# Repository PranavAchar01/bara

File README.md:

<p align="center">
  
</p>

<p align="center">
  <b>Describe a device. Get it built from real parts.</b><br />
  A <b>Cal Hacks 13.0</b> project by Pranav Achar and Nithin Aruswamy · <a href="https://tangible.parts">tangible.parts</a>
</p>

---

<p align="center">
  <b><a href="https://youtu.be/Tw2DHo8dgQ8">▶ Watch the 3-minute demo</a></b>
</p>

Type "a wireless split keyboard with an OLED" and watch it come together. Bara picks real parts, lays them out in 3D, sculpts a case, routes a real KiCad board, and writes the firmware, explaining every choice as it goes. Then you change it in plain words or with your voice, and every edit is checked before it lands.

## Inside the app

<table>
  <tr>
    <td width="50%"><br /><b>Start</b> · describe a device in one line</td>
    <td width="50%"><br /><b>Edit</b> · click a part to swap, recolour, move, or ask</td>
  </tr>
  <tr>
    <td><br /><b>Explode</b> · pull it apart and see every layer</td>
    <td><br /><b>Board</b> · a routed KiCad PCB that passes DRC</td>
  </tr>
  <tr>
    <td><br /><b>Simulate</b> · run the generated firmware and press the keys</td>
    <td><br /><b>Library</b> · past builds and 135 open-source boards</td>
  </tr>
</table>

## Meet Bara

Bara is the agent who builds with you: an ink oval with two eyes, nothing else. It walks onto the canvas, hovers over the part it's choosing, and shows how it feels through motion alone. Click a part to swap it, recolour it, move it, or ask about it. Hold <kbd>Space</kbd> to talk. Every change lands as a version you can undo.

<br clear="right" />

## What it builds

Each of these started as one sentence.

## Tangible vs a general chat model

We gave Claude (Fable 5.1, a fresh chat on claude.ai) the prompt "an ergonomic mouse with a PAW3212 optical sensor, two main click switches, a scroll wheel encoder and an nRF52840 board", and compared what it produced with a Tangible build of the same kind of mouse.

| | Claude (Fable 5.1) | Tangible |
|---|---|---|
| First reply | Text only: a pin map and a bill of materials (33 s) | An existing library build, so no new run was timed |
| 3D model | Only after a follow-up asking for one: a Three.js page you can rotate (150 s) | Built in |
| Exploded view | Only after a second follow-up (59 s) | Built in |
| Part shapes | Procedural boxes and cylinders | KiCad library part models on a routed PCB |
| Board and export | A PCB shape and a shell, with no routed board and no export | A routed KiCad board and a case |

It took Claude two follow-ups to get to an exploded 3D view. That viewer does work well: you can rotate it, X-ray it, flip to the underside and drag an explode slider.

The Tangible build here is an existing, larger version of the mouse from the library (extra thumb switches, a slide switch, an IMU, a proximity sensor and a battery connector), not a fresh run against the same prompt. It also lists one push button, where the prompt asked for two main click switches. Screenshots were taken at different sizes: Claude at 1200x1189 with its chat pane, Tangible at 1600x1000.

<table>
  <tr>
    <td width="50%"><br /><b>Claude, assembled</b></td>
    <td width="50%"><br /><b>Claude, exploded</b></td>
  </tr>
  <tr>
    <td><br /><b>Tangible, assembled</b></td>
    <td><br /><b>Tangible, exploded</b></td>
  </tr>
</table>

In a separate measurement for the demo video, a general coding agent given a handheld-console prompt took 50.4 s and answered with text and a browser game.

## How a build works

```mermaid
flowchart LR
  P([Your prompt]) --> S[Scout open designs]
  S --> C[Classify and compose]
  C --> L[Place parts]
  L --> E[Sculpt the case]
  E --> B[Route the board]
  B --> F[Write firmware]
  F --> R([3D build you can edit])
  R -. voice or text edits .-> C

  classDef you fill:#2563EB,color:#fff,stroke:#2563EB
  classDef claude fill:#D97757,color:#fff,stroke:#D97757
  classDef kicad fill:#161616,color:#fff,stroke:#161616
  class S you
  class C,F claude
  class B kicad
```

<table>
  <tr><td>🔵 <b>Scout</b></td><td>Finds open designs that already exist, so Bara reuses before it invents.</td></tr>
  <tr><td>🟠 <b>Compose</b></td><td>Breaks the device into function blocks and picks one real part for each, with reasons.</td></tr>
  <tr><td>⚫ <b>Board</b></td><td>pcbnew builds it, Freerouting routes it, kicad-cli checks it. DRC errors trigger a re-route.</td></tr>
  <tr><td>✅ <b>Checks</b></td><td>Electrical, mechanical, and a vision judge that asks if it actually looks like the device.</td></tr>
</table>

## Sponsor tools

| | Tool | What it does in Bara |
|---|---|---|
| 🟠 | **Anthropic Claude** | The engineer behind every decision. Sonnet 5.5 classifies the prompt, asks clarifying questions, picks parts (schema-locked to real part IDs), writes firmware, judges the render, and handles edits. Claude Code built the product, including an overnight loop that ran our test prompts, found root causes, and pushed fixes. |
| 🟣 | **Figma** | All design, made through Claude Code and the Figma MCP. FigJam teardown, a full design system with the agent's moods, a Make prototype of explode and focus, and design tokens pulled straight into `tokens.css`. |
| 🟢 | **OpenAI** | Bara's voice. gpt-4o-mini-tts speaks with a written personality, and gpt-4o-transcribe listens, hinted with the build's part names so "SSD1306" comes through right. |
| 🔵 | **You.com** | The first search on every build. Finds open designs with a real KiCad board, plus photos of the real product so the case looks right. |
| 🟩 | **Apify** | The Open Hardware Scout Actor ([actors/](actors/bara-hardware-scout)). Fallback search, and it prices every part so the BOM has live stock and buy links. |
| 🔶 | **Cerebras** | A fast path for quick, constrained calls, with Claude as backup and keyword rules as the last resort, so a build always finishes. |

## Fit check (OpenCV 5 on AWS)

Built for the OpenCV AI Competition 2026, after Cal Hacks. Lay a printed ArUco marker next to the space a device has to fit and take one photo from above. OpenCV 5 on AWS Lambda (arm64 Graviton) rectifies the photo and measures the space in millimetres. The agent then proposes the next step: build to that size, shrink the current case, cut its height, or retake the photo if it can't trust it. Nothing changes until you approve.

On synthetic photos with known sizes the mean error is 0.42 mm (p95 1.4 mm), and bad photos get a retake request in 29 of 30 cases. The [technical report](docs/hackathons/opencv26/report.md) covers the method, the deployment, the evaluation and its limits.

```bash
cd server && uv run pytest tests/test_vision.py
uv run python scripts/vision_eval.py ../docs/hackathons/opencv26/eval
uv run python aws/deploy.py        # needs AWS credentials in the environment
```

## Run it

You need [uv](https://docs.astral.sh/uv/), [pnpm](https://pnpm.io), and Node.

```bash
scripts/dev.sh
```

That starts the engine on `127.0.0.1:8790` and the app on http://localhost:5173. No keys? Open http://localhost:5173/?mock=1 to replay a recorded build in the browser.

Live builds need `ANTHROPIC_API_KEY`, plus KiCad 10 and Freerouting for boards. `OPENAI_API_KEY`, `YOU_API_KEY`, `APIFY_TOKEN`, and `CEREBRAS_API_KEY` are optional. Keys come from the environment only.

<details>
<summary>Tests and repo layout</summary>

```bash
cd server && uv run pytest
cd web && pnpm test
scripts/e2e.sh
```

```
spec/      the contract between app and engine (SPEC.md, schemas, fixtures)
server/    FastAPI engine (src/bara), catalog and assets in data/
web/       Vite + React + React Three Fiber app
actors/    the Apify Open Hardware Scout
scripts/   dev, e2e, deploy, and render scripts
```

</details>

## Disclosure

Before the event we wrote the spec and a labelled set of test prompts, and ran a small routing experiment to check the idea was feasible. None of that experiment's code is in this repo. We used Nithin's public UI skill library, the same one we used in Etch. Everything in this repo was written at Cal Hacks 13.0.

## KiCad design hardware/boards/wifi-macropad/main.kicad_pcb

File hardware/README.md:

# Hardware gate

Tangible turns a sentence into a gadget: parts, a KiCad schematic and PCB, and a printed shell.
This folder holds boards Tangible generated, and the gate every board passes before it ships.

- `boards/<board>/` holds `main.kicad_pcb`, `main.kicad_sch`, `main.kicad_pro` and `fp-lib-table`.
  Library paths use `${TANGIBLE_ROOT}`, `${TANGIBLE_SOURCES}` and `${KICAD10_FOOTPRINT_DIR}`.
- `policy.json` sets the gate (0 DRC errors, 0 ERC errors, 0 unconnected items, 0 blocked parts)
  and maps each footprint library to its source and licence.

Run it locally (needs `kicad-cli` 10):

```sh
PYTHONPATH=server/src python3 -m bara.hwci check hardware/boards --policy hardware/policy.json
PYTHONPATH=server/src python3 -m bara.hwci fab hardware/boards --out hw-fab
```

`check` writes `hw-report/`: `results.json`, `gate.md` (the merge request note), `junit.xml`,
`gl-code-quality-report.json` and a CycloneDX hardware BOM per board in `hbom/`.

The same checks are an MCP server for GitLab Duo (`.gitlab/duo/mcp.json`):

```sh
PYTHONPATH=server/src python3 -m bara.hwci.mcp_server --root hardware/boards --policy hardware/policy.json
```

Tools: `list_boards`, `check_board`, `board_parts`, `export_fab`.

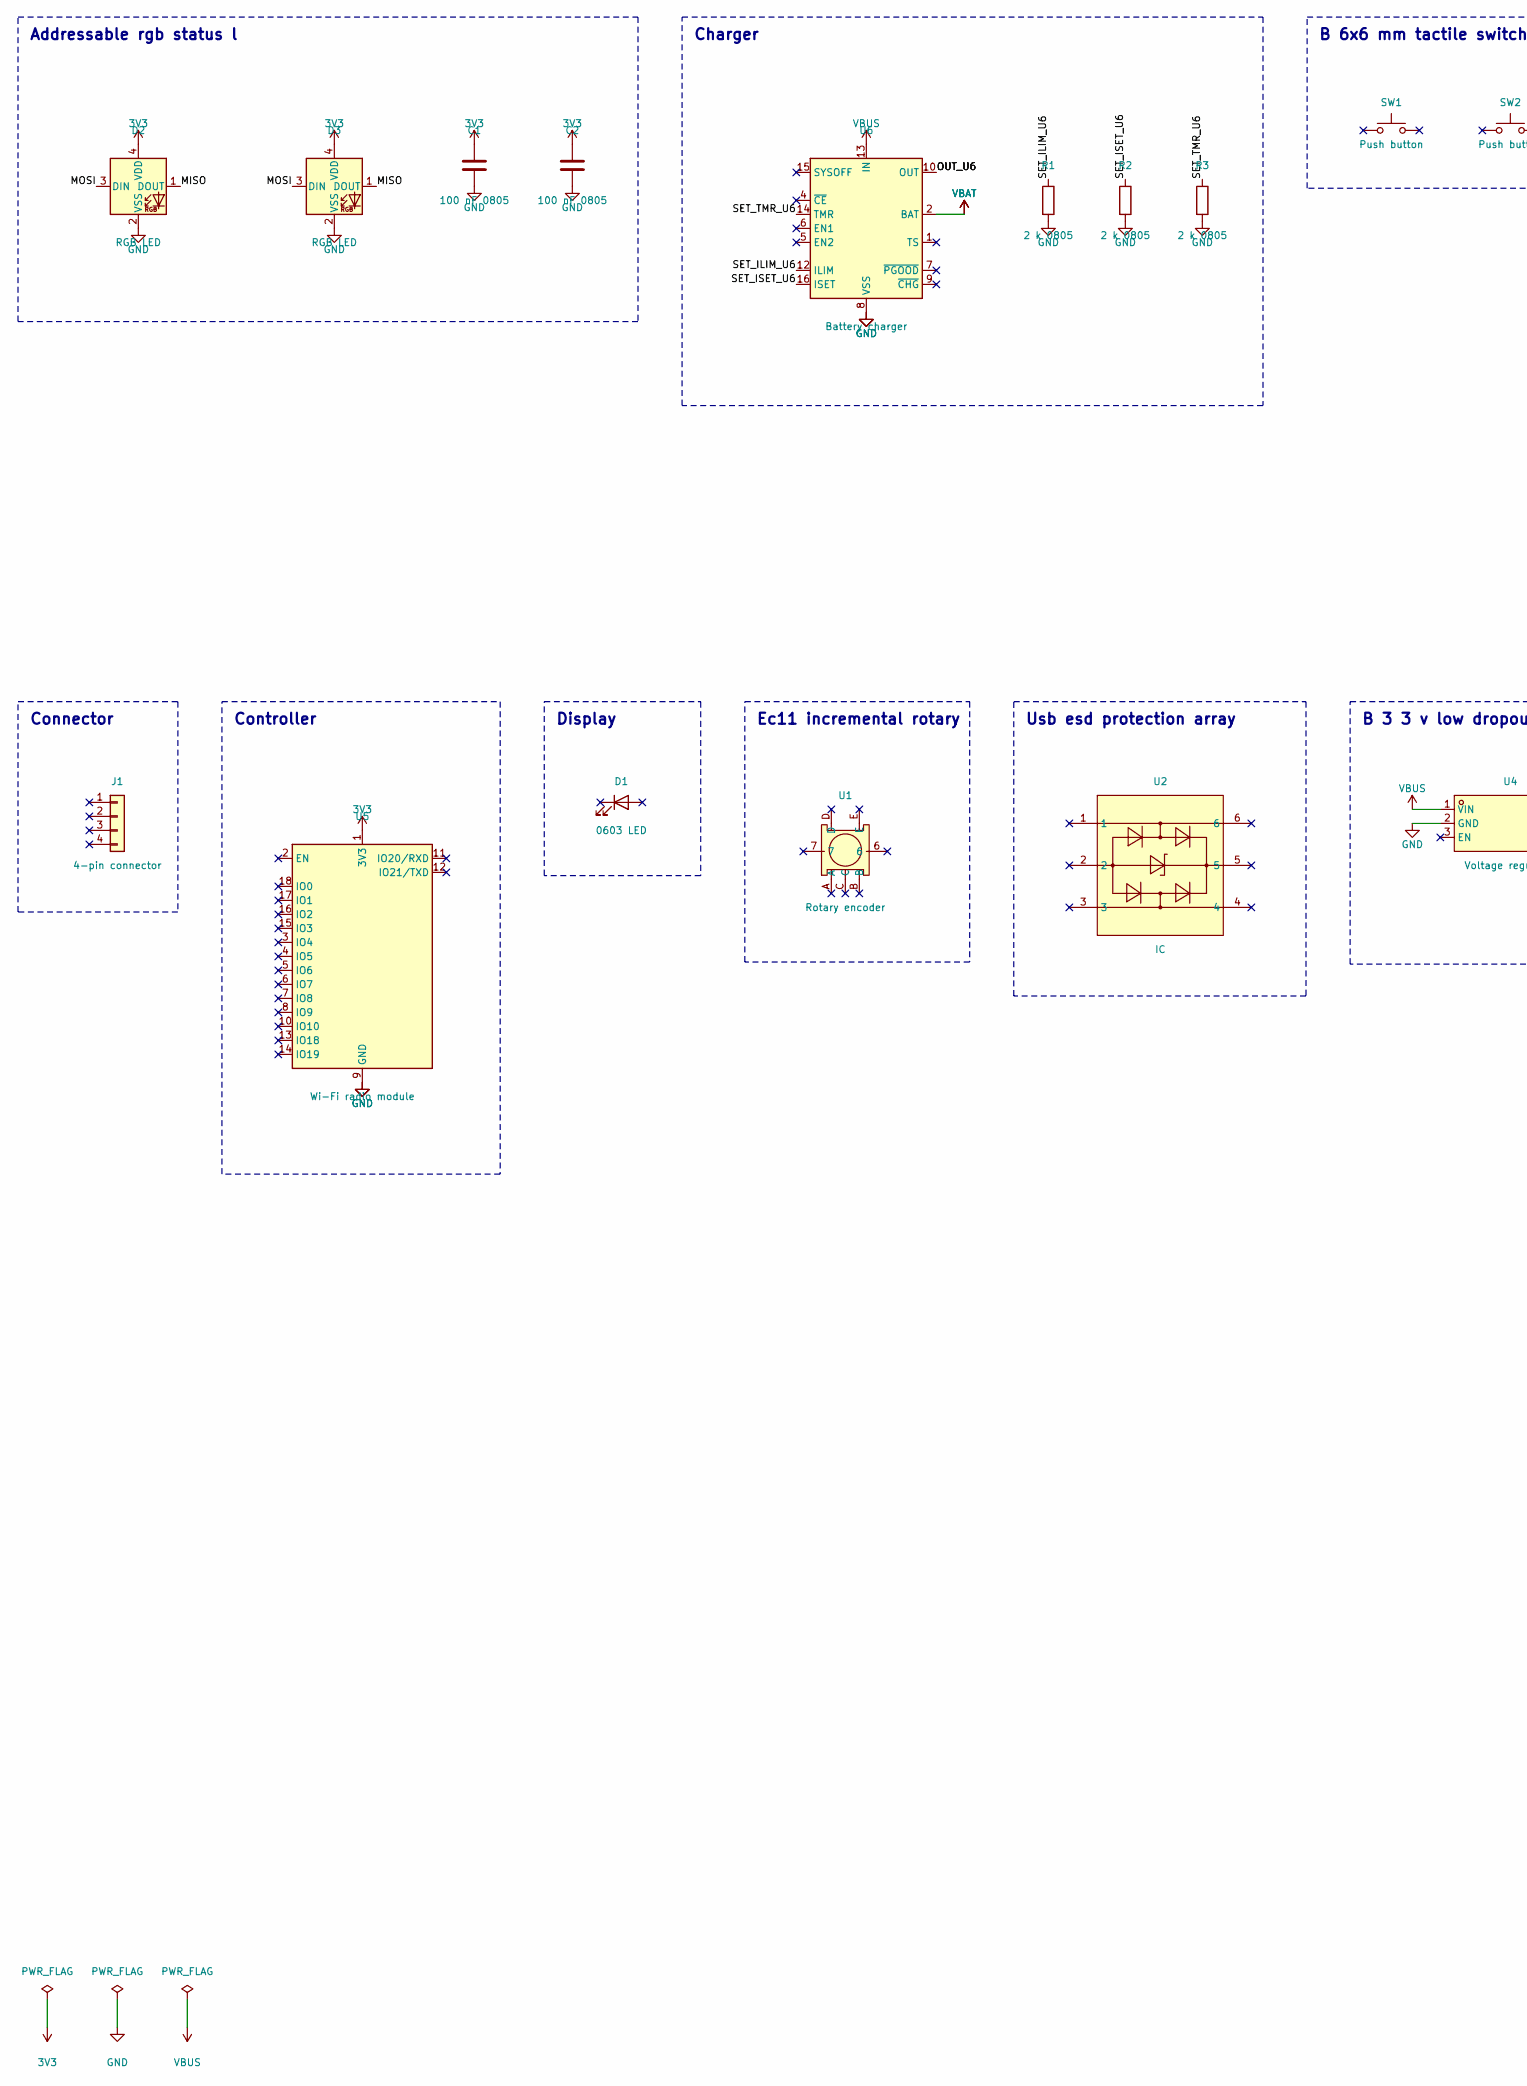
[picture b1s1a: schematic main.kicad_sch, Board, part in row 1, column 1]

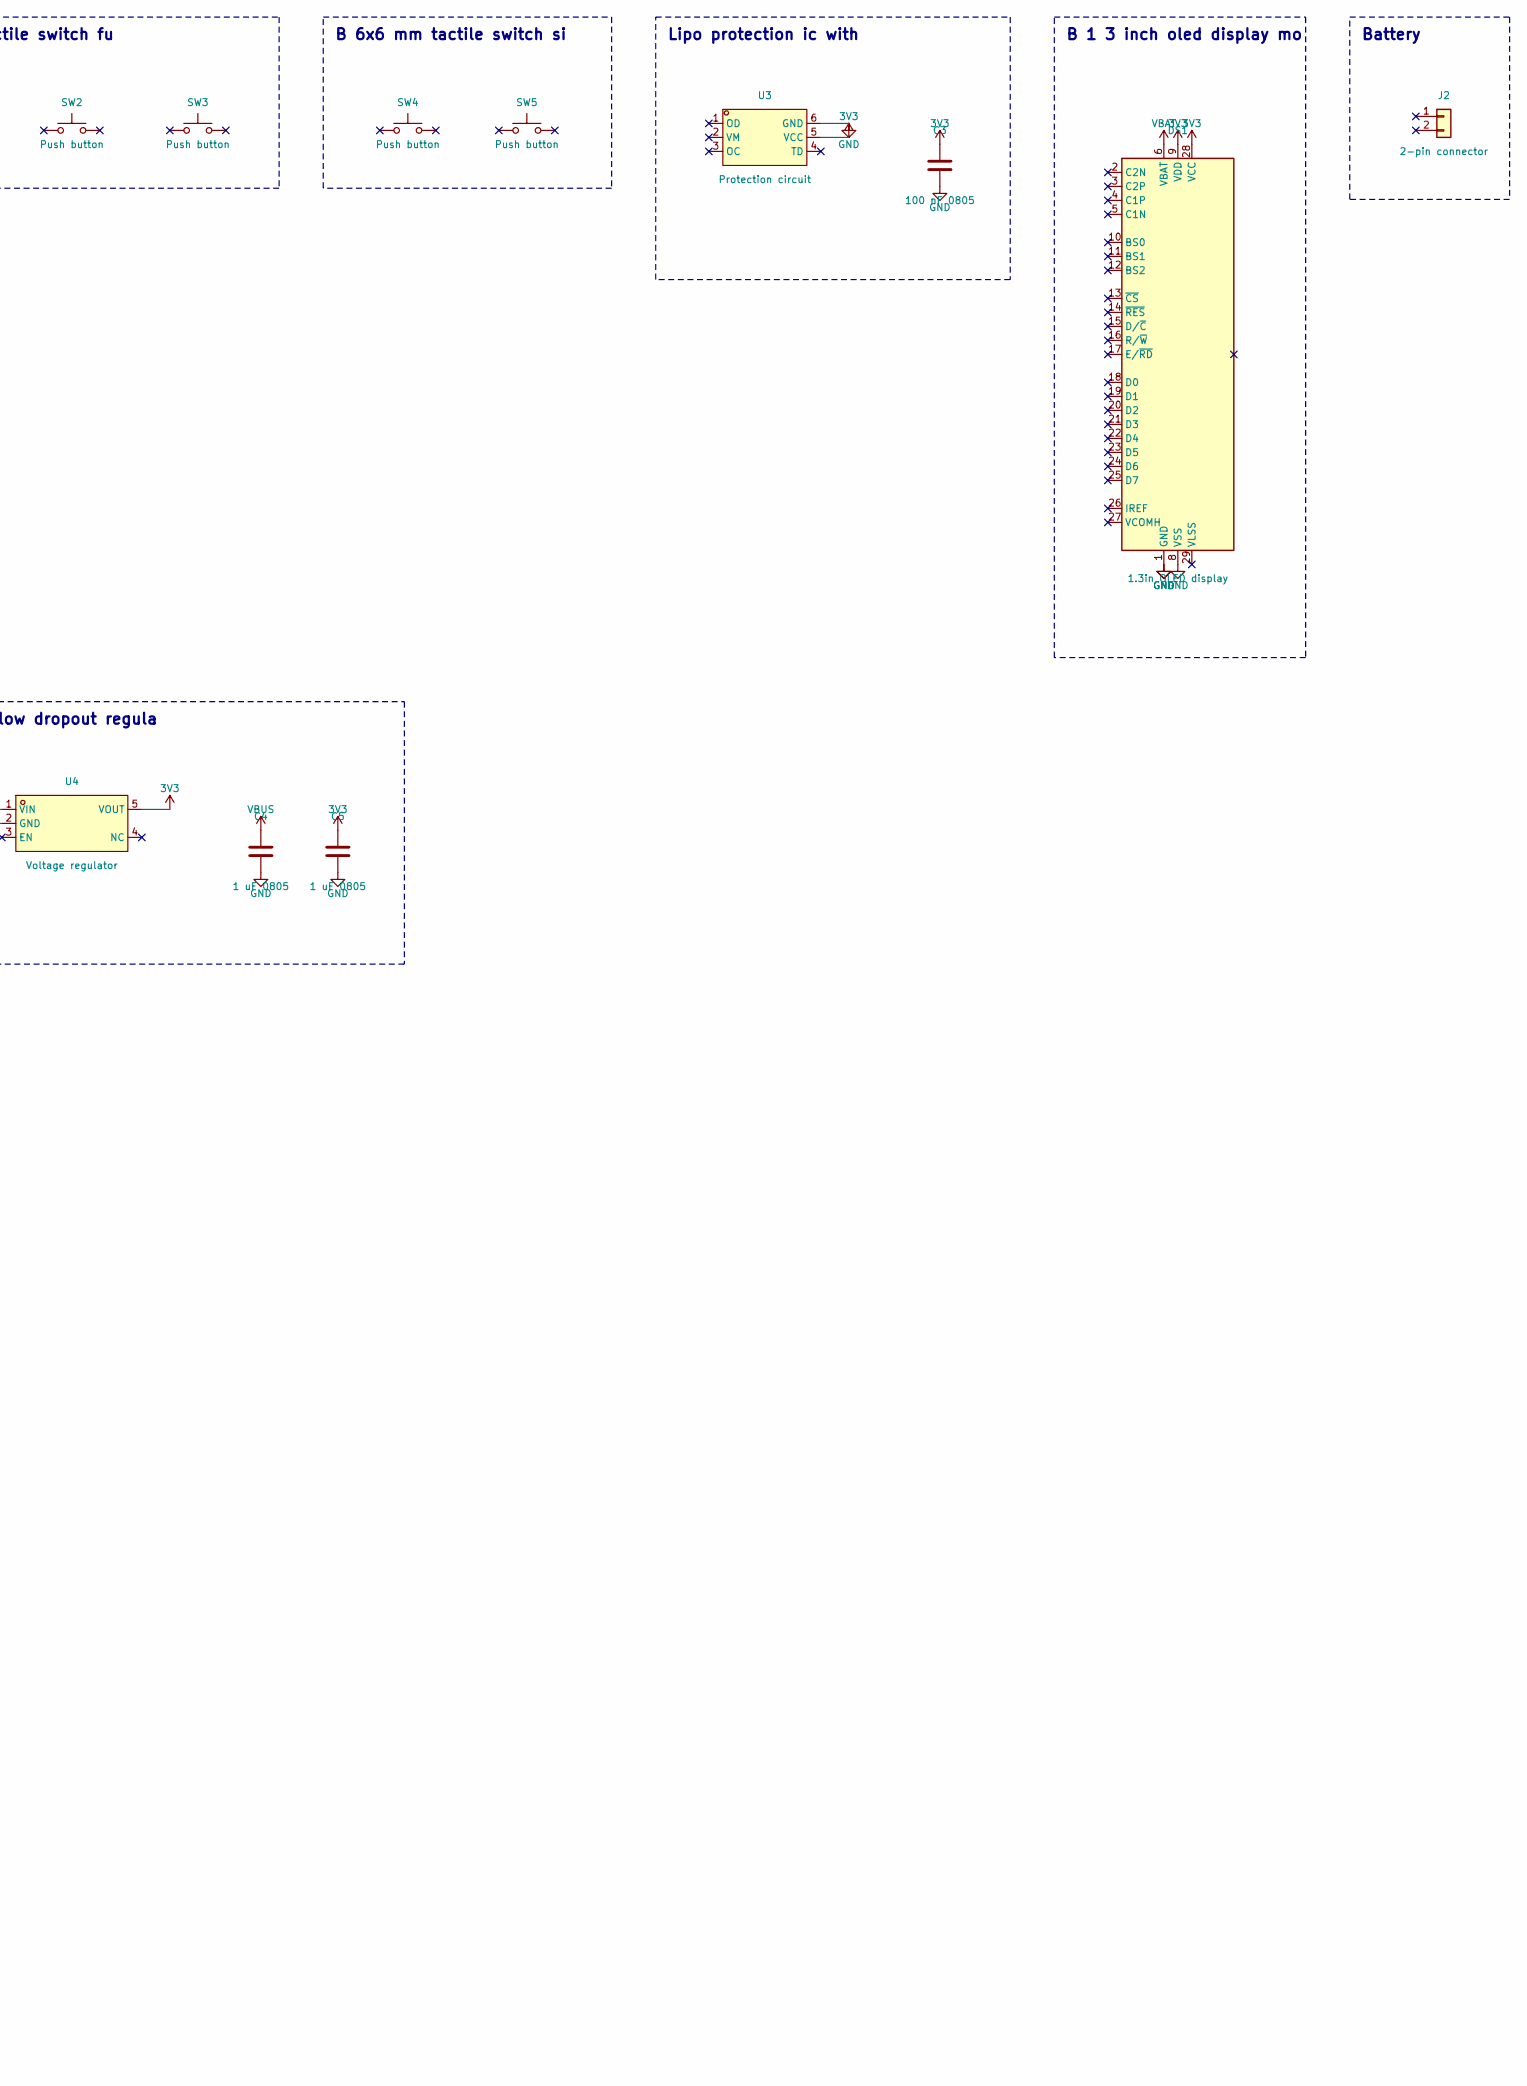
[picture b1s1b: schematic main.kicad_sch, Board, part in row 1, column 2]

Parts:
C1, C2, C3: 100 nF 0805; C_0805_2012Metric
C4, C5: 1 uF 0805; C_0805_2012Metric
D1: 0603 LED; LED_0603_1608Metric
D2, D3: RGB LED; LED_WS2812B-2020_PLCC4_2.0x2.0mm
DS1: 1.3in OLED display; OLED-128O064D
J1: 4-pin connector; JST_SH_SM04B-SRSS-TB_1x04-1MP_P1.00mm_Horizontal
J2: 2-pin connector; JST_PH_S2B-PH-K_1x02_P2.00mm_Horizontal
R1, R2, R3: 2 k 0805; R_0805_2012Metric
SW1, SW2, SW3, SW4, SW5: Push button; SW_PUSH_6mm
U1: Rotary encoder; C370970
U2: IC; C7519
U3: Protection circuit; C351410
U4: Voltage regulator; C51118
U5: Wi-Fi radio module; ESP32-C3-WROOM-02
U6: Battery charger; VQFN-16-1EP_3x3mm_P0.5mm_EP1.68x1.68mm

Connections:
3V3: C1.1, C2.1, C3.1, C5.1, D2.4 (VDD), D3.4 (VDD), DS1.9 (VDD), DS1.28 (VCC), U3.5 (VCC), U4.5 (VOUT), U5.1 (3V3)
GND: C1.2, C2.2, C3.2, C4.2, C5.2, D2.2 (VSS), D3.2 (VSS), DS1.1 (GND), DS1.8 (VSS), DS1.30 (GND), R1.2, R2.2, R3.2, U3.6 (GND), U4.2 (GND), U5.9 (GND), U5.19 (GND), U6.8 (VSS), U6.17 (VSS)
MISO: D2.1 (DOUT), D3.1 (DOUT)
MOSI: D2.3 (DIN), D3.3 (DIN)
OUT_U6: U6.10 (OUT), U6.11 (OUT)
SET_ILIM_U6: R1.1, U6.12 (ILIM)
SET_ISET_U6: R2.1, U6.16 (ISET)
SET_TMR_U6: R3.1, U6.14 (TMR)
VBAT: DS1.6 (VBAT), U6.2 (BAT), U6.3 (BAT)
VBUS: C4.1, U4.1 (VIN), U6.13 (IN)

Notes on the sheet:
Addressable rgb status l
Charger
B 6x6 mm tactile switch fu
B 6x6 mm tactile switch si
Lipo protection ic with
B 1 3 inch oled display mo
Battery
Connector
Controller
Display
Ec11 incremental rotary
Usb esd protection array
B 3 3 v low dropout regula

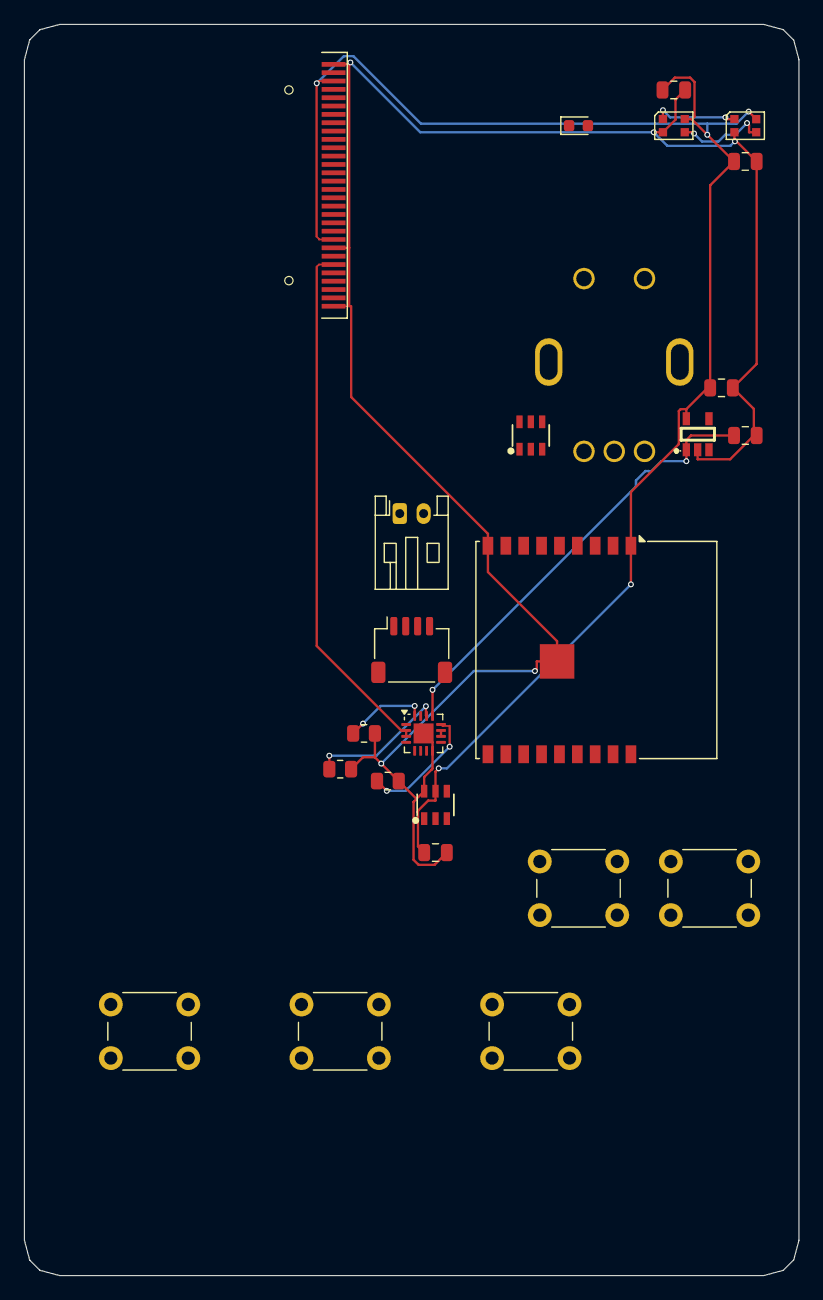
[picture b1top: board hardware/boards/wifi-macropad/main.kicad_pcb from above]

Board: 2 copper layers, 65.0 x 105.0 mm, 25 parts (1 on the bottom side), 10 nets.

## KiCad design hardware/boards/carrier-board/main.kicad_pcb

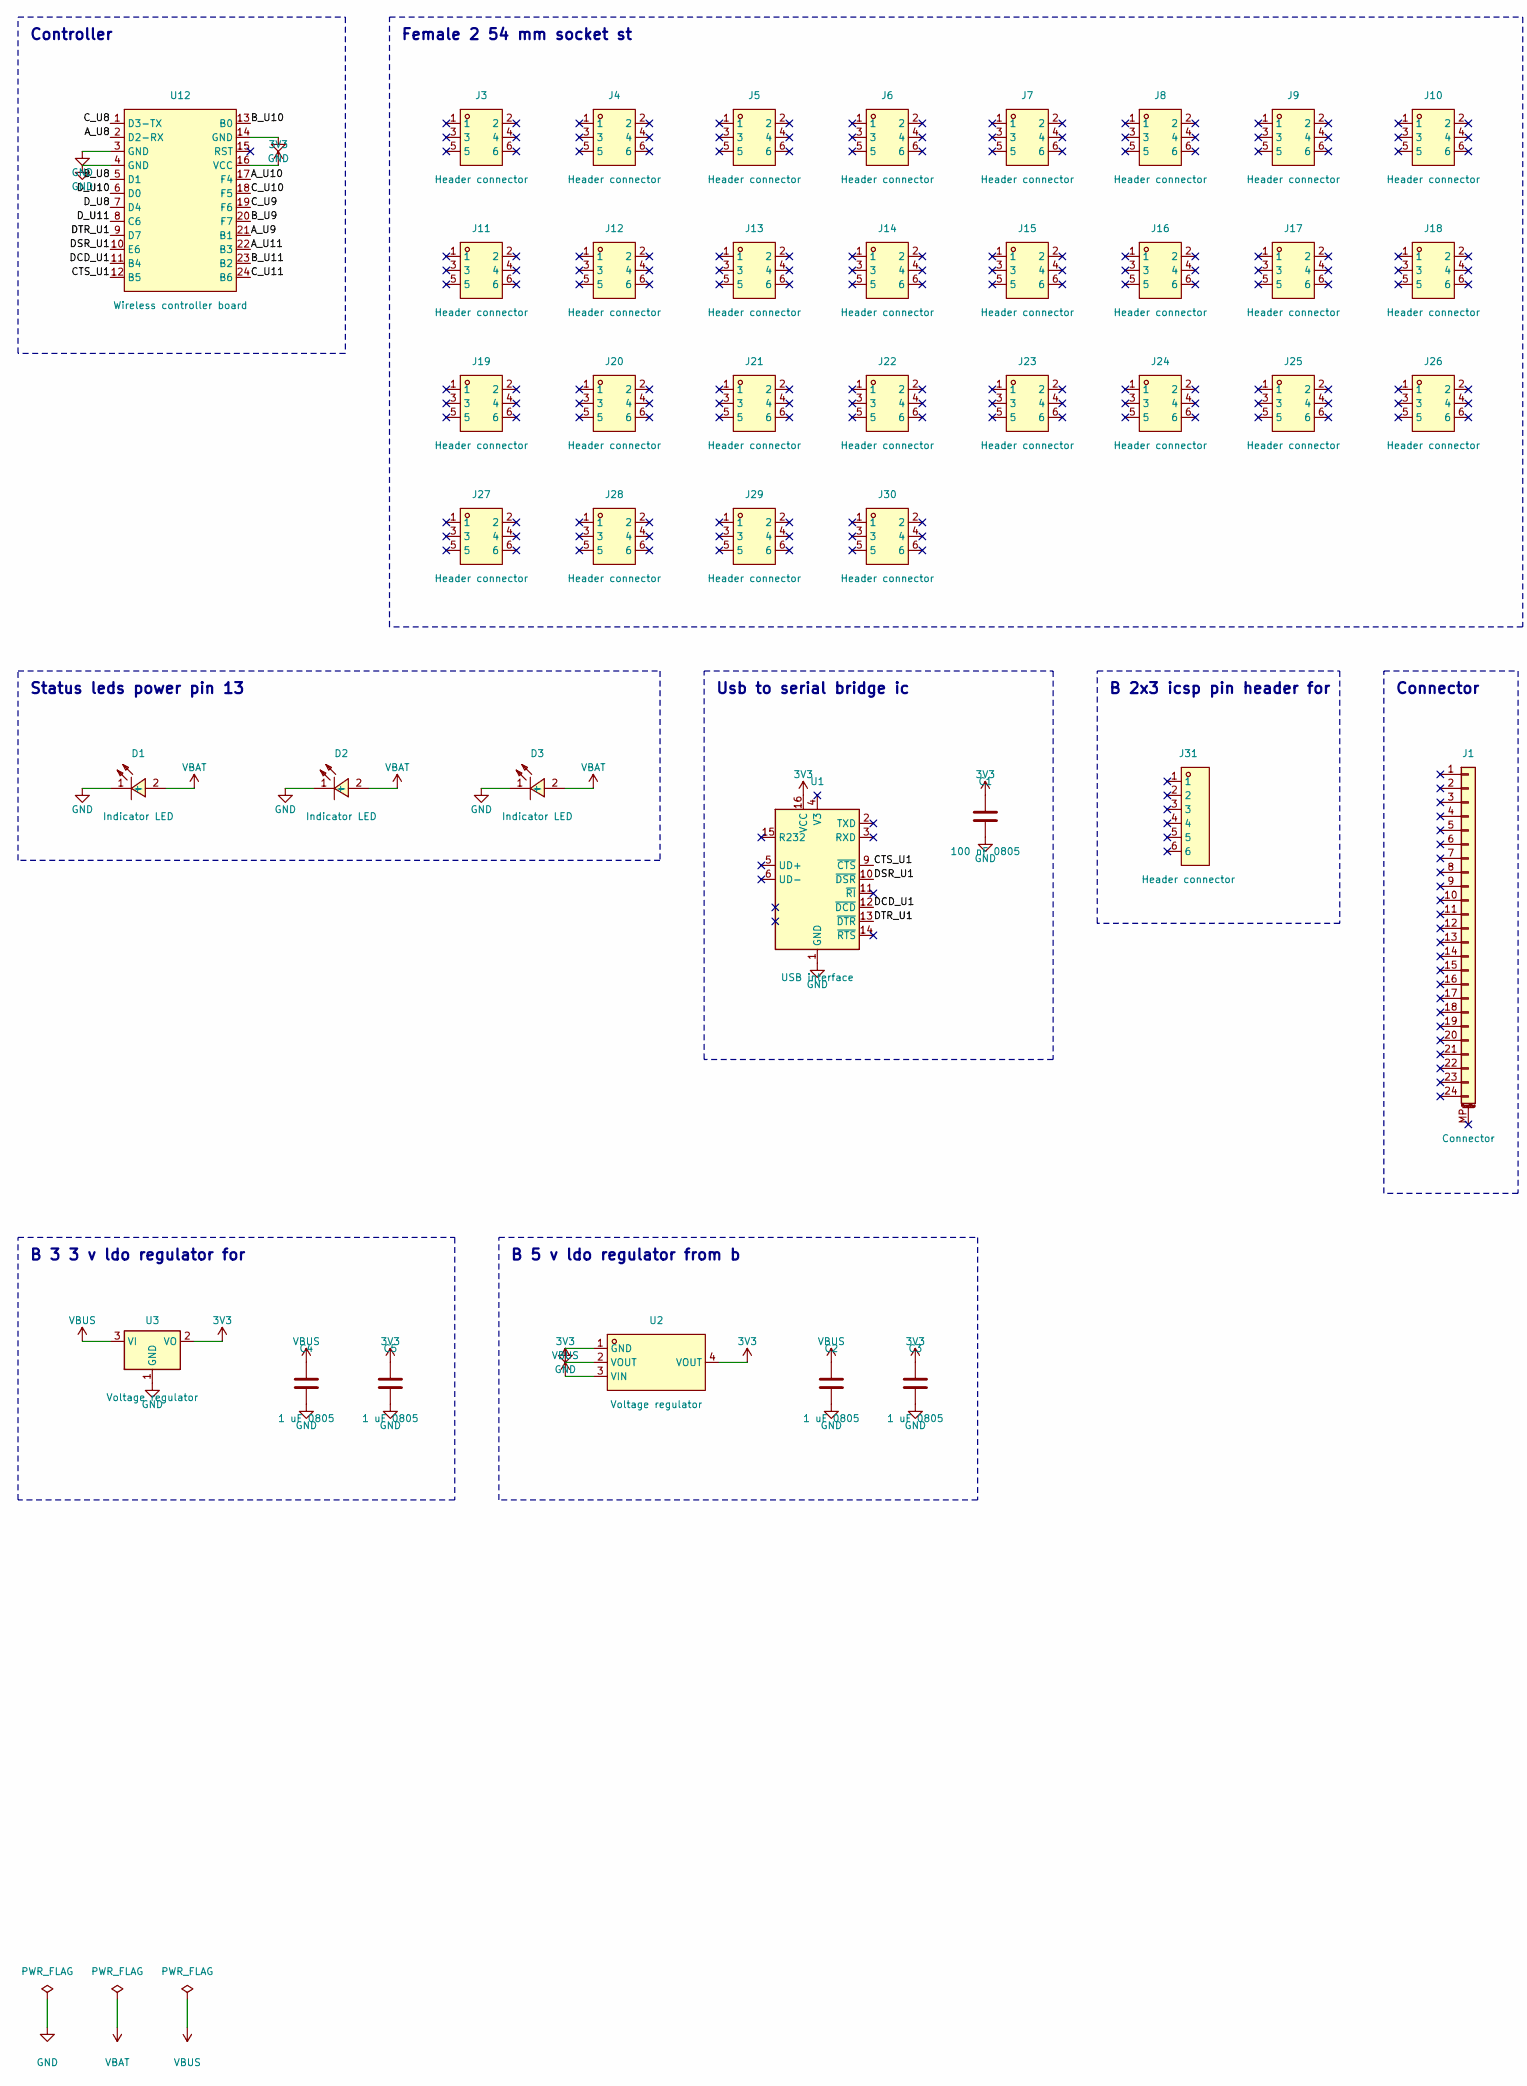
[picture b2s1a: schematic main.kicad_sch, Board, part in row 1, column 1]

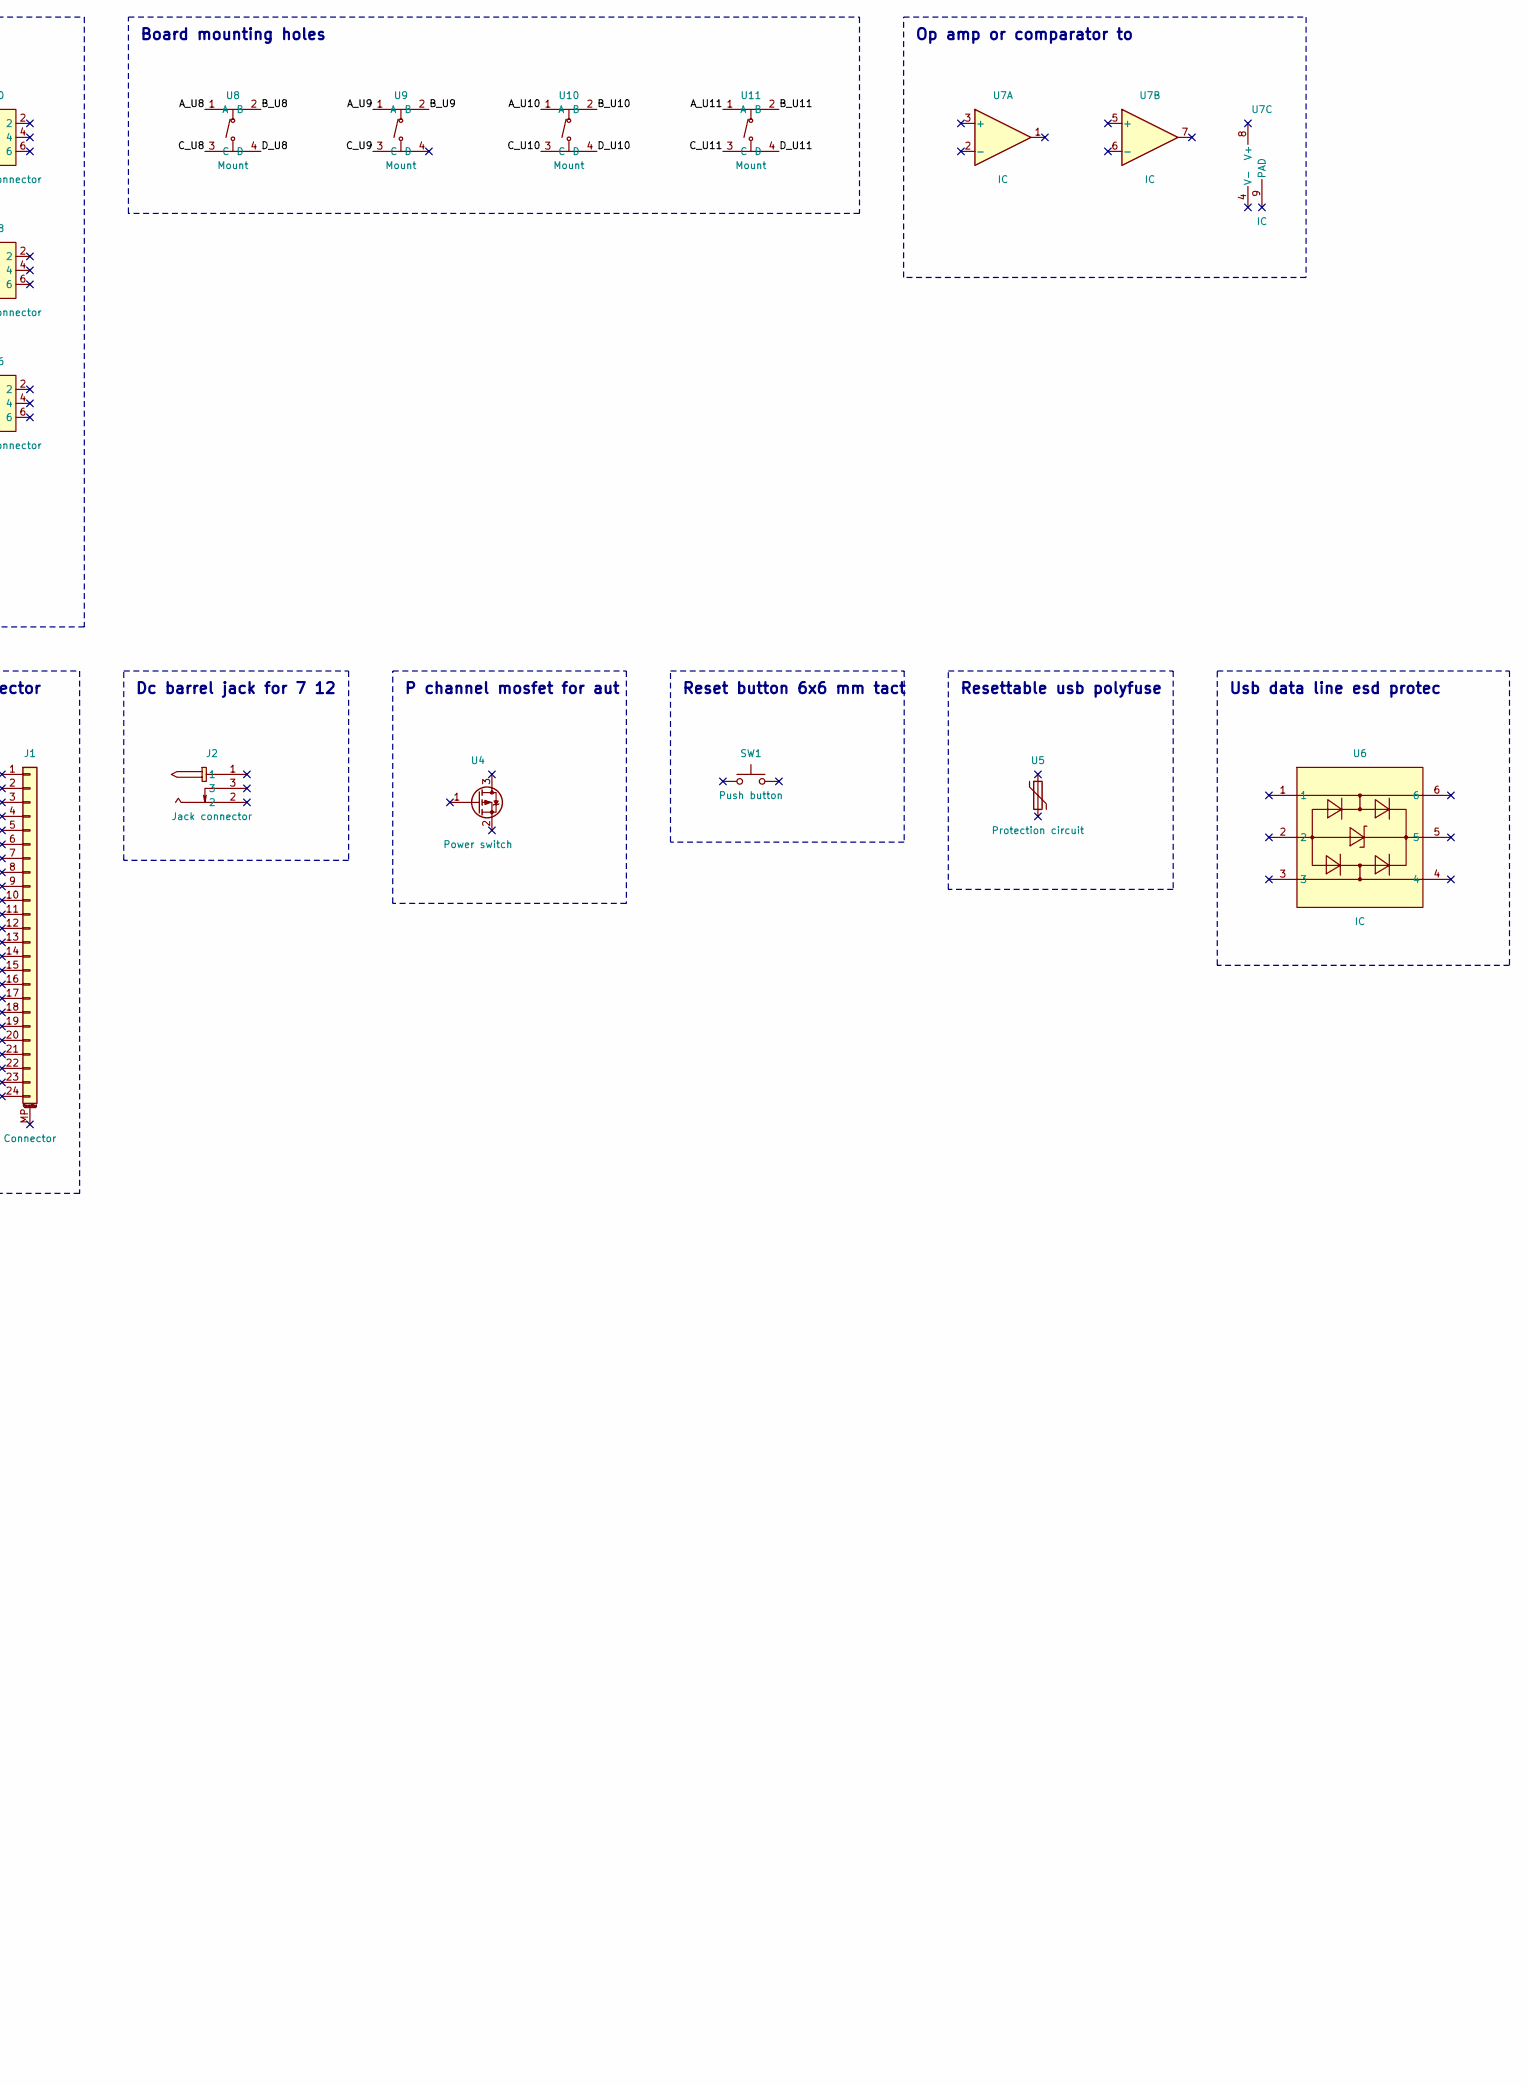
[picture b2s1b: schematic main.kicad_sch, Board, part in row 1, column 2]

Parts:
C1: 100 nF 0805; C_0805_2012Metric
C2, C3, C4, C5: 1 uF 0805; C_0805_2012Metric
D1, D2, D3: Indicator LED; C125094
J1: Connector; Hirose_FH12-24S-0.5SH_1x24-1MP_P0.50mm_Horizontal
J2: Jack connector; C5250216
J3, J4, J5, J6, J7, J8, J9, J10, J11, J12, J13, J14, J15, J16, J17, J18, J19, J20, J21, J22, J23, J24, J25, J26, J27, J28, J29, J30: Header connector; C5140604
J31: Header connector; C492405
SW1: Push button; SW_SKHLLCA010
U1: USB interface; SOIC-16_3.9x9.9mm_P1.27mm
U2: Voltage regulator; C6187
U3: Voltage regulator; SOT-223-3_TabPin2
U4: Power switch; SOT-23
U5: Protection circuit; Fuse_1812_4532Metric
U6: IC; C7519
U7: IC; DFN-8-1EP_2x2mm_P0.5mm_EP1.05x1.75mm
U8, U9, U10, U11: Mount; C318884
U12: Wireless controller board; ProMicro_USBup

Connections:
3V3: C1.1, C3.1, C5.1, U1.16 (VCC), U2.2 (VOUT), U2.4 (VOUT), U3.2 (VO), U12.16 (VCC)
A_U8: U8.1 (A), U12.2 (D2-RX)
A_U9: U9.1 (A), U12.21 (B1)
A_U10: U10.1 (A), U12.17 (F4)
A_U11: U11.1 (A), U12.22 (B3)
B_U8: U8.2 (B), U12.5 (D1)
B_U9: U9.2 (B), U12.20 (F7)
B_U10: U10.2 (B), U12.13 (B0)
B_U11: U11.2 (B), U12.23 (B2)
CTS_U1: U1.9 (~CTS), U12.12 (B5)
C_U8: U8.3 (C), U12.1 (D3-TX)
C_U9: U9.3 (C), U12.19 (F6)
C_U10: U10.3 (C), U12.18 (F5)
C_U11: U11.3 (C), U12.24 (B6)
DCD_U1: U1.12 (~DCD), U12.11 (B4)
DSR_U1: U1.10 (~DSR), U12.10 (E6)
DTR_U1: U1.13 (~DTR), U12.9 (D7)
D_U8: U8.4 (D), U12.7 (D4)
D_U10: U10.4 (D), U12.6 (D0)
D_U11: U11.4 (D), U12.8 (C6)
GND: C1.2, C2.2, C3.2, C4.2, C5.2, D1.1 (-), D2.1 (-), D3.1 (-), U1.1 (GND), U2.1 (GND), U3.1 (GND), U12.3 (GND), U12.4 (GND), U12.14 (GND)
VBAT: D1.2 (+), D2.2 (+), D3.2 (+)
VBUS: C2.1, C4.1, U2.3 (VIN), U3.3 (VI)

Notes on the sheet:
Controller
Female 2 54 mm socket st
Board mounting holes
Op amp or comparator to
Status leds power pin 13
Usb to serial bridge ic
B 2x3 icsp pin header for
Connector
Dc barrel jack for 7 12
P channel mosfet for aut
Reset button 6x6 mm tact
Resettable usb polyfuse
Usb data line esd protec
B 3 3 v ldo regulator for
B 5 v ldo regulator from b

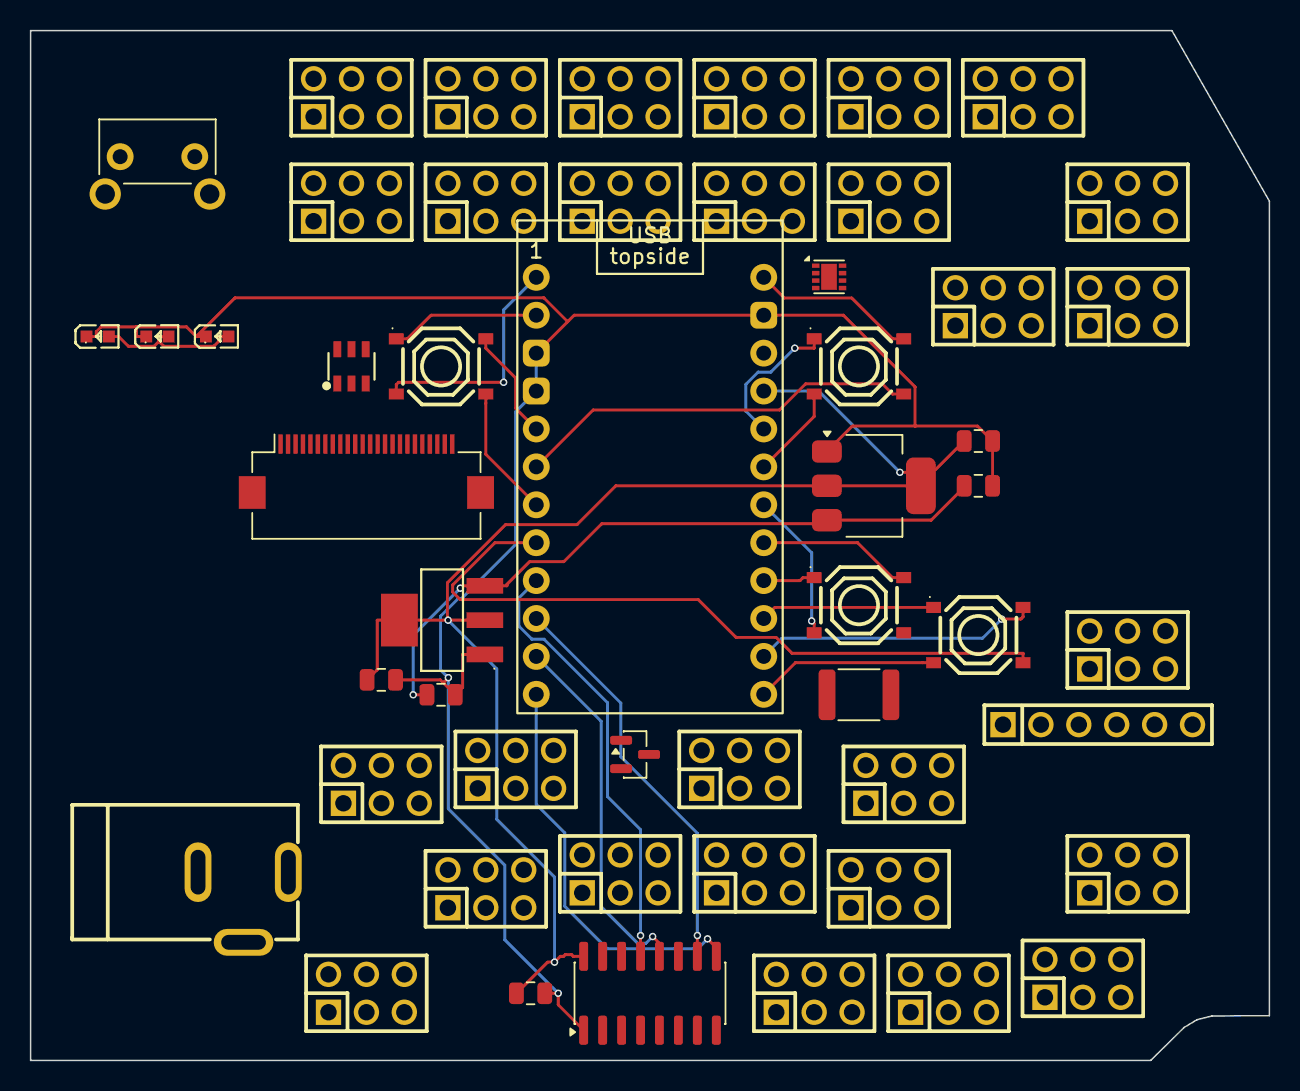
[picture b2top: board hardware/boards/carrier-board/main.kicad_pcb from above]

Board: 2 copper layers, 83.0 x 69.0 mm, 52 parts (0 on the bottom side), 23 nets.
